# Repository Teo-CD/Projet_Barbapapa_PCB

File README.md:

# Projet Barbapapa - Carte électronique

Le Projet Barbapapa est un projet surprise qui réunit des anciens JINs.

L'une des parties de ce projet est un objet intéractif, ce dépôt en contient
la conception électroniques, réalisée avec [KiCad](https://www.kicad.org/).

# Objectifs

La carte électronique doit permettre la détection de tags RFID, le contrôle 
d'un écran LCD, de LEDs RGB, ainsi que l'utilisation d'un haut-parleur.

Elle doit permettre une opération connectée à un ordinateur, comme indépendante.

# État

**Révision 1.0**  

La production de la carte a été lancée, mais pas encore testée.

La versionnement de forme X.Y se lit comme suit:
 - X : Version mise en production (avec 1 comme première production)
 - Y : Révision suivant la mise en production (remis à 0 quand X augmente)

# Choix

## Fabricant

La carte a été conçue pour être fabriquée par JLCPCB en double couche avec une carte de 0.8mm d'épaisseur. Les marges
du design ont donc été pensées pour leurs capacités de fabrication.  
Le choix du 0.8mm est essentiellement pour faciliter l'atteinte de la bonne impédance pour les pistes D+ et D- de l'USB.  
JLCPCB a aussi le gros avantage d'être très bon marché, en passant en double couche les PCBs devraient coûter à peine
quelques livres.

## Carte microcontrôleur

La teensy 4.1 a été choisie pour la flexibilité de ses interfaces et des bibliothèques disponnibles.  
La carte elle-même est bien trop puissante pour l'application, qui ne nécessite pas la capacité de calcul d'un Cortex-M7,
mais cela réduira les contraintes lors du développement du firmware pour faire tourner les différents éléments.

En particulier, les bibliothèques audio de la teensy sont assez réputées et ont servies pour faire différentes pédales
d'effet, et la présence d'un port microSD déjà intégré sur la carte rend le stockage des animations pour le LCD et des
fichiers audios bien plus simple.

## Alimentation

Une des contraintes de conception était la possibiltié d'utiliser l'objet de façon indépendante d'un ordinateur. Il a donc
fallut intégrer une batterie capable de tenir la charge du système.

L'élément le plus consommateur ici est l'amplificateur audio. Bien que la majeure partie du temps il ne consomme presque rien,
les pics de courant demandés lors du jeu audio ont poussé au choix d'une batterie Li-Ion et d'un régulateur pouvant soutenir
2A de courant continu.

Les batteries Li-Ion ont l'avantage monter à 4.2V à pleine charge, il est donc possible de les charger par USB. Cela évite
l'utilisation de piles non-rechargeables, que je voulais éviter. Elles permettent aussi de débiter un courant suffisant pour
alimenter tout le système, ce qui est rarement le cas des piles jetables de toutes façons.

Le système est donc alimenté par la batterie, parfois complémenté par le chargeur qui fournit jusqu'à 500mA pour la charger.
Seule la Teensy est alimentée directement par la batterie, tout le reste du système est derrière le régulateur 3.3V (tension
logique de la Teensy).

L'alimentation à la Teensy est contrôlée par un interrupteur externe branché sur `SW2`, puis cette dernière contrôle l'activation
du régulateur 3.3V. Elle peut lire la tension fournie par la batterie et décider de couper le système si nécessaire pour la
préserver.  

### À noter

Le gros du système est protégé d'une inversion de polarité de la batterie Li-Ion par une diode. Cependant, le chargeur lui-même
ne l'est pas. Cette décision à été prise car l'inversion ne devrait pas être trop commune, le réceptacle étant polarisé et indiqué,
mais aussi pour la chute de tension supplémentaire que ça aurait apporté.

***Ne pas mettre la batterie à l'envers !***

## Périphériques

La carte est conçue pour la connexion d'un écran LCD de Nokia 5110 pour son style à gros pixels et d'un module NFC.  

Le module NFC choisi est le RC522 pour sa capacité à gérer de multiples tags dans sa zone de détection et ainsi permettre de
poser plusieurs figurines sur la zone en même temps.  

Au cas où la zone de détection s'avère trop faible ou que la connexion du module NFC et du module LCD au même bus SPI soit
problématique, deux alternatives ont été prévues sur la carte :  
 1. La possibilité d'utiliser du soft-SPI pour le LCD
 2. La sortie d'un deuxième bus SPI indépendant pour un deuxième module NFC en parallèle

L'amplificateur a été choisi pour son entrée I2S (signal audio numérique) et son circuit d'amplification très complet et
auto-suffisant, ne nécessitant pas grand chose de plus que quelques condensateurs et résistances pour le choix de fonctionnement.  
C'est un MAX98357A, il existe aussi sous forme de module entre autre par Sparkfun comme "I2S Audio Breakout".  

Deux autres séries de broches sont présentes : une pour brancher un câble FTDI et avoir accès à la série de la Teensy directement
(seules les broches TX/RX et la masse sont connectées) et un trois broches pour contrôler des LEDs RGB addressables style neopixel.

# License

Les éléments présents dans ce dépôt sont Open Source Hardware, sous license [CERN Open Hardware Licence Version 2 - Weakly Reciprocal](https://ohwr.org/cern_ohl_w_v2.txt).

# Crédits

Carte conçue par Téo-CD, avec les conseiles de Victor Védie, François Charles, Lucas Molia.

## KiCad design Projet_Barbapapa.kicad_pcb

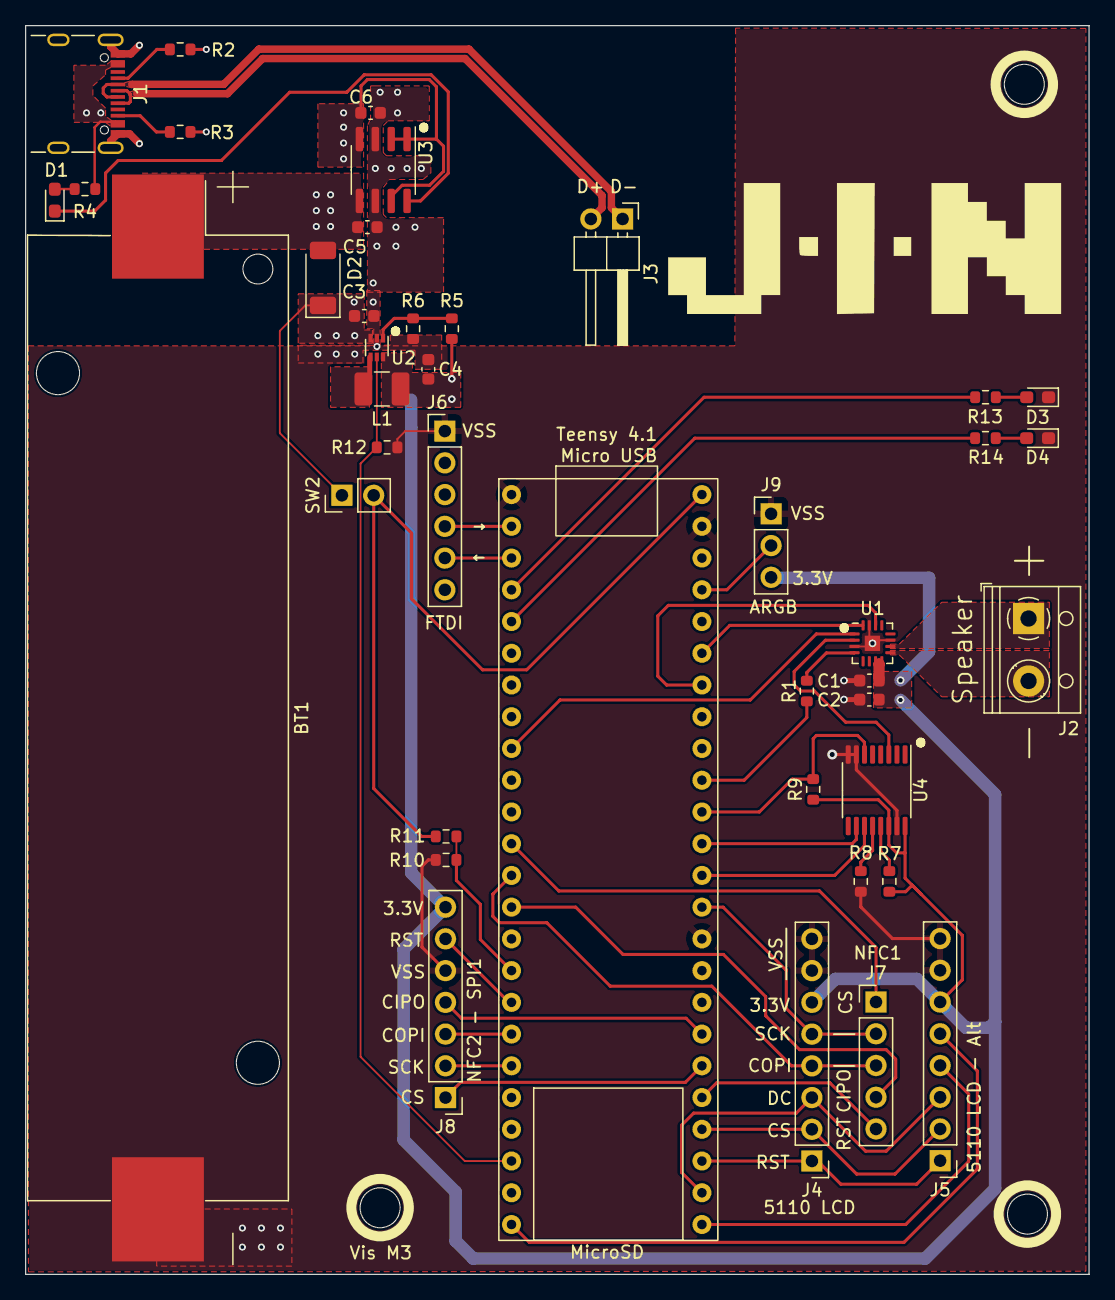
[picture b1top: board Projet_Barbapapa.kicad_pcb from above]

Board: 2 copper layers, 85.1 x 99.9 mm, 44 parts (0 on the bottom side), 51 nets.

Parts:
BT1: Battery_Cell; BatteryHolder_Keystone_1042_1x18650
C1: CAP_0603_100nF_50V; CAP_0603
C2, C3, C4, C5, C6: CAP_0603_10uF_50V; CAP_0603
D1, D3, D4: LED; LED_0603_1608Metric_Pad1.05x0.95mm_HandSolder
D2: PMEG3050EP-QX; D_SOD-128
H1, H2, H3: MountingHole; MountingHole_3.2mm_M3
J1: USB_C_Receptacle_USB2.0; USB_C_Receptacle_GCT_USB4105-xx-A_16P_TopMnt_Horizontal
J2: Speaker; TerminalBlock_RND_205-00012_1x02_P5.00mm_Horizontal
J3: Conn_01x02; PinHeader_1x02_P2.54mm_Horizontal
J4: LCD SPI; PinHeader_1x08_P2.54mm_Vertical
J5: LCD Soft SPI; PinHeader_1x08_P2.54mm_Vertical
J6: Random FTDI; PinHeader_1x06_P2.54mm_Vertical
J7: NFC1; PinHeader_1x05_P2.54mm_Vertical
J8: NFC2; PinHeader_1x07_P2.54mm_Vertical
J9: RGB_LED; PinHeader_1x03_P2.54mm_Vertical
L1: IND_1.5uH_5A_20%; L_1210_3225Metric_Pad1.42x2.65mm_HandSolder
R1: RES_0603_634K_1%; RES_0603
R2, R3, R9, R12: RES_0603_5K1_1%; RES_0603
R4, R13, R14: RES_0603_200_1%; RES_0603
R5, R10: RES_0603_200k_1%; RES_0603
R6: RES_0603_44K2_1%; RES_0603
R7, R8, R11: RES_0603_100K_1%; RES_0603
SW2: Power switch; PinHeader_1x02_P2.54mm_Vertical
Teensy 4.1: Teensy 4.1
U1: MAX98357A/B; TQFN-16-1EP_3x3mm_P0.5mm_EP1.23x1.23mm
U2: AP61201Z6-7 buck; SOT-563
U3: MAX1811; SOIC-8_3.9x4.9mm_P1.27mm
U4: CD4051B; TSSOP-16_4.4x5mm_P0.65mm

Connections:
/ARGB_Data: J9.2, Teensy 4.1.23
/Audio/AMP_GAIN0: Teensy 4.1.14, U4.11 (A)
/Audio/AMP_GAIN1: Teensy 4.1.15, U4.10 (B)
/Audio/AMP_GAIN_EN: R9.2, Teensy 4.1.16, U4.6 (INH)
/Audio/Amp_enable: R1.1, Teensy 4.1.17
/Audio/BCLK: Teensy 4.1.21 (A7), U1.16 (BCLK)
/Audio/LRCLK: Teensy 4.1.20 (A6), U1.14 (LRCLK)
/Audio/Speaker_N: J2.2, U1.9 (OUTP)
/Audio/Speaker_P: J2.1, U1.10 (OUTN)
/Audio_OUT: Teensy 4.1.7 (OUT1A), U1.1 (DIN)
/BAT_SNS: R10.2, R11.1, Teensy 4.1.24 (A10)
/DBG_LED_1: R13.1, Teensy 4.1.2 (OUT2)
/DBG_LED_2: R14.2, Teensy 4.1.3 (LRCLK2)
/LCD connectors/LCD_COPI_ALT: J5.4, Teensy 4.1.33 (MCLK2)
/LCD connectors/LCD_CS: J4.2, J5.2, Teensy 4.1.36 (CS)
/LCD connectors/LCD_DC: J4.3, J5.3, Teensy 4.1.34 (RX8)
/LCD connectors/LCD_RST: J4.1, J5.1, Teensy 4.1.35 (TX8)
/LCD connectors/LCD_SCK_ALT: J5.5, Teensy 4.1.32 (OUT1B)
/NFC1_RST: J7.5, Teensy 4.1.37
/NFC2_CS: J8.1, Teensy 4.1.38 (A14)
/NFC Connectors/NFC1_CS: J7.1, Teensy 4.1.10 (CS)
/NFC Connectors/NFC2_RST: J8.6, Teensy 4.1.25 (A11)
/Power and USB/BATT_LOAD: BT1.1 (+), C5.2, D2.2 (A), U3.5 (BATT)
/Power and USB/BATT_SAFE: C3.1, D2.1 (K), SW2.1 (A), U2.3 (VIN)
/Power and USB/USB_D_N: J1.A7 (D-), J1.B7 (D-), J3.1
/Power and USB/USB_D_P: J1.A6 (D+), J1.B6 (D+), J3.2
/Power and USB/VBUS: C6.2, J1.A4 (VBUS), J1.A9 (VBUS), J1.B4 (VBUS), J1.B9 (VBUS), R4.2, U3.1 (SELV), U3.2 (SELI), U3.4 (IN), U3.7 (EN)
/Power and USB/VIN: R11.2, SW2.2 (B), Teensy 4.1.60 (Vin)
/Reg_en: R12.1, Teensy 4.1.30, U2.5 (EN)
/SPI1_CIPO: J8.4, Teensy 4.1.39 (A15)
/SPI1_COPI: J8.3, Teensy 4.1.26 (A12)
/SPI1_SCK: J8.2, Teensy 4.1.27 (A13)
/SPI_CIPO: J7.4, Teensy 4.1.12 (CIPO)
/SPI_COPI: J4.4, J7.3, Teensy 4.1.11 (COPI)
/SPI_SCK: J4.5, J7.2, Teensy 4.1.13 (SCK)
unnamed: D1.2 (A), R4.1
unnamed: D1.1 (K), U3.8 (~CHG)
unnamed: D3.2 (A), R13.2
unnamed: D4.2 (A), R14.1
unnamed: J1.A5 (CC1), R2.1
unnamed: J1.B5 (CC2), R3.2
unnamed: J6.4, Teensy 4.1.0 (RX1)
unnamed: J6.5, Teensy 4.1.1 (TX1)
unnamed: U1.2 (~GAIN_SLOT), U4.3 (X)
unnamed: R1.2, U1.4 (~SD_MODE)
unnamed: R5.1, R6.2, U2.1 (FB)
unnamed: L1.1, U2.4 (SW)
unnamed: R7.2, U4.13 (X0)
unnamed: R8.2, U4.12 (X3)
VDD: C1.1, C2.1, C4.2, J4.6, J5.6, J8.7, J9.3, L1.2, R5.2, R7.1, R9.1, U1.7 (VDD), U1.8 (VDD), U2.6 (OUT), U4.14 (X1), U4.16 (VDD)
VSS: BT1.2 (-), C1.2, C2.2, C3.2, C4.1, C5.1, C6.1, D3.1 (K), D4.1 (K), J1.A1 (GND), J1.A12 (GND), J1.B1 (GND), J1.B12 (GND), J1.S1 (SHIELD), J4.7, J4.8, J5.7, J5.8, J6.1, J8.5, J9.1, R2.2, R3.1, R6.1, R8.1, R10.1, R12.2, Teensy 4.1.50 (GND), Teensy 4.1.57 (GND), Teensy 4.1.59 (GND), U1.3 (GND), U1.11 (GND), U1.15 (GND), U1.17 (GND), U2.2 (GND), U3.3 (GND), U3.6 (GND), U4.7 (VEE), U4.8 (VSS), U4.15 (X2)

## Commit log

2023-06-19 Première révision carte complète
    La carte est planifiée et routée avec un minimum de choses fonctionelles
    Il reste beaucoup de questions:
    - Comment faire la dissipation thermique proprement ?
    - Où/comment mettre les vias ?
    - Routage OK ?
    - Coupure à basse charge de batterie ?
2023-06-22 Améliorations après retour Victor
    Allumage du régulateur maintenant géré par la teensy
    Compaction de la carte pour rentrer sur 100x100mm
    Ajout des trous de montage
    Routage de la puissance du port USB maintenant sans boucle !
    Un peu plus d'espace pour l'ampli'
    Routage de l'ampli' avec des plans sur la sortie et une via par
2023-06-22 Inversion de la bobine de régulateur
    180° à la bobine du régulateur pour faciliter le routage et le placement
    Plus d'espace autour du régulateur.
2023-06-25 License under CERN-OHL-W
2023-06-25 Rev 0.3: Passage sur deux couches
    Passage sur deux couches, ajustement de l'impédance pour l'USB.
    Reroutage de l'alimentation côté USB
    Ajout de beaucoup de silk
    Quelques ajustements de nets pour la lisbilité
    Ajout de LEDs de debug
    Plan de masse sur le top
2023-06-25 Étoffe le README avec les choix et raisonnements
2023-06-26 Corrections et expansion de masque
    Quelques ajustements de routage au cas où, pour VIN et une branche thermique
    sur VSS.
    Ajustement de la marge sur le plan de masse du dessus (plus grande).
    Vérification de l'expansion de masque pour le passage à 2 couches.
2023-06-26 Mentionne KiCad dans le README
2023-06-26 Prépare pour production de la 1.0
2023-06-26 Change le Qr pour archive.org
